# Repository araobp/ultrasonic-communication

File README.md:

**(Nov 2, 2018) I am going to rework on this project**

---
---
# Learning DSP with ultrasonic communications

## Background and motivation

STMicro gave me STM32L4(Arm Cortex-M4) evaluation board and a pair of MEMS microphones for free at [a trade show held in Makuhari city](https://www.st.com/content/st_com/en/about/events/events.html/techno-frontier-2018.html), Chiba, Japan. Thanks a lot to STMicro!

As an IoT hobyyist, I am becoming interested in DSP with MEMS mic.

Also thanks to this: https://github.com/y2kblog/NUCLEO-L476RG_DFSDM_PDM-Mic.

## Project goal

I am a DSP beginner, so I learn DSP by doing: realize "low-power narrow area networking" by cheap DSP and MEMS mic.

## My work so far

#### Project documentation

==> [Specification](https://docs.google.com/presentation/d/e/2PACX-1vSd3PQnKqmKbjcGNyNh_gygd175jgfzZYH5iwcEPqmmgiy7k3yYzqqHzfs7u-95jm_9hHgc0ugAvv2U/pub?start=false&loop=false&delayms=3000)

#### Platform: STM32L4 platform and FFT test code on MEMS mic

==> [Platform](./experiments/PLATFORM.md)

==> [Test code](./experiments/basic)

#### Mathematical formula expressing ultrasonic wave

I tested frequency-hopping to transmit data over ultra-sonic, resulting in very bad performance at low SNR in a noisy room. So I decided to employ chirp modulation in this project.

==> [Formula](./misc/Formula.ipynb)

#### Developing my original MEMS mic shield

I developed my original shield with Knowles MEMS mic:

- Knowles MEMS mic
- Character LCD
- LED (red)
- Tactile switche (reset)

#### Pinout of STM32L476RG

#### Working code

Code of the ultrasonic receiver running on STM32L476RG (Arm Cortex-M4L) and the original expansion board:

==> [Code](./receiver)

## Next challenge: I/Q modulation

I already made the code, but it did not fit into the RAM, so I will reduce the number of samples to 1024.

But the resolution of FFT w/ I/Q modulation will be still much better than the current implementation (FFT of 2048 samples w/o I/Q modulation).

## Experiments I made over the past month

I have made several experiments over the past month to study how data can be transmitted over ultra-sonic wave: FSK, hopping and chirp. The conclusion is to try Chirp modulation to fight with noise.

#### Ultrasonic communications experiment (FSK modulation)

==> [Experiment](./experiments/EXPERIMENT.md)

==> [Test code](./experiments/ultracom)

#### Ultrasonic communications experiment (Chirp modulation)

==> [Experiment2](./experiments/EXPERIMENT2.md)

==> [Test code](./experiments/chirp)

#### Ultrasonic communications experiment (Chirp modulation with compression)

==> [Experiment3](./experiments/EXPERIMENT3.md)

#### Ultrasonic communications experiment (time frame synchronization)

==> [Experiment4](./experiments/EXPERIMENT4.md)

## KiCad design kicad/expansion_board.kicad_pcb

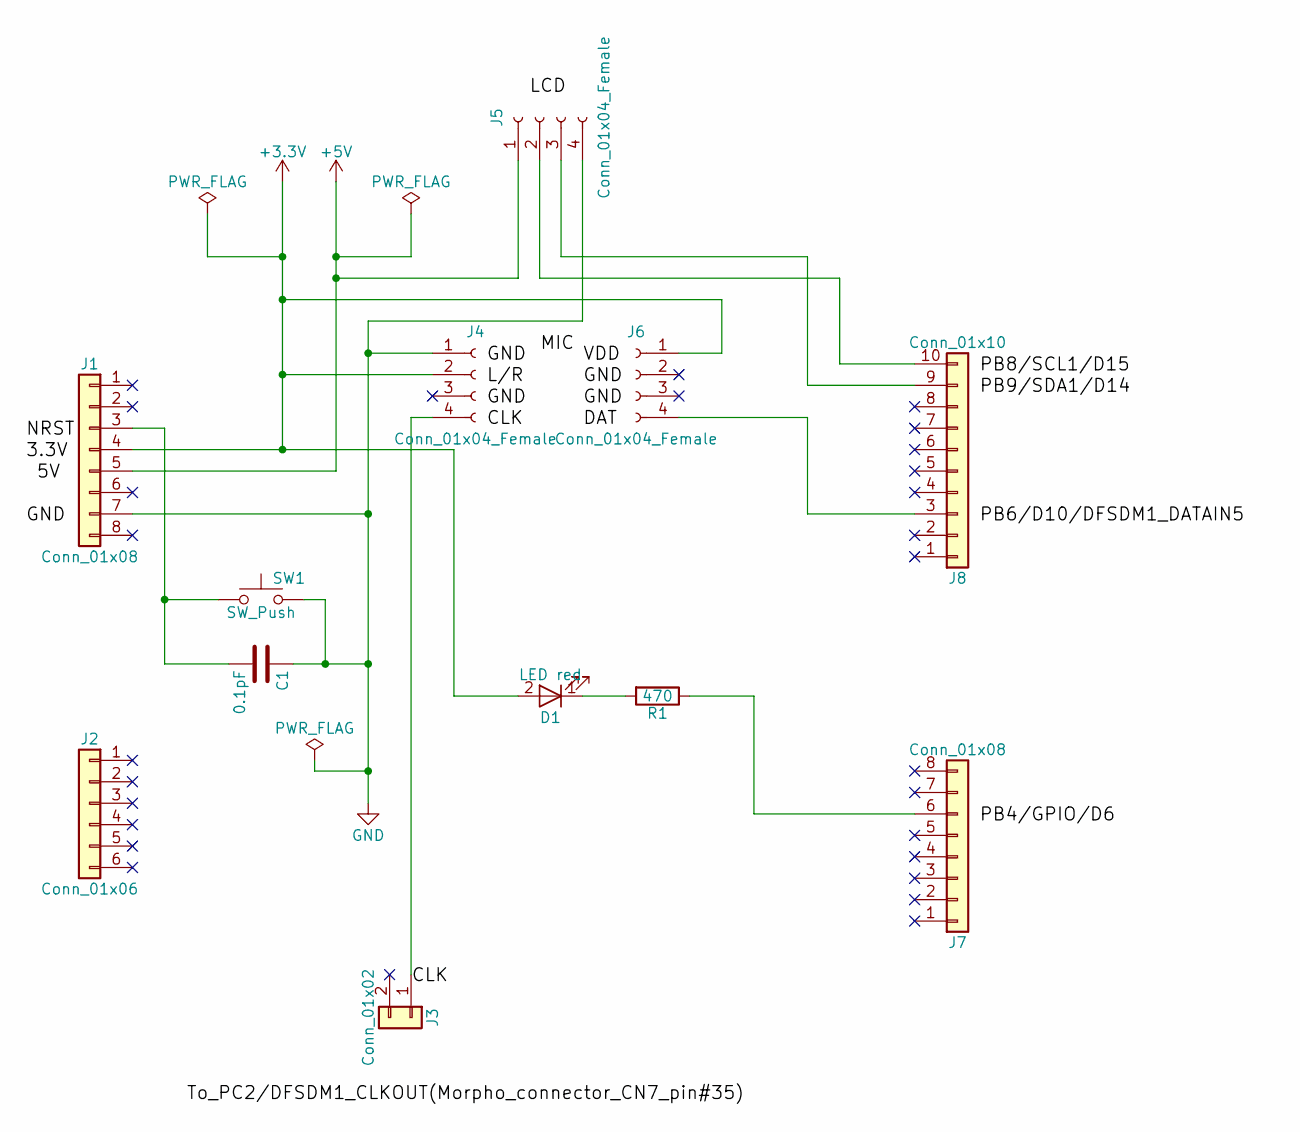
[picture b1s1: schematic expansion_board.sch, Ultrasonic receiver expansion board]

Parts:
C1: 0.1pF; Capacitor
D1: LED red; LED
J1, J7: Conn_01x08; Pin Header 8P
J2: Conn_01x06; Pin Header 6P
J3: Conn_01x02; Pin Header 2P
J4, J5, J6: Conn_01x04_Female; Pin Header 4P
J8: Conn_01x10; Pin Header 10P
R1: 470; Register
SW1: SW_Push; Tactile_switch_4P

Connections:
+3V3: D1.2 (A), J1.4, J4.2, J6.1
+5V: J1.5, J5.1
GND: C1.1, J1.7, J4.1, J5.4, SW1.2
unnamed: C1.2, J1.3, SW1.1
unnamed: D1.1 (K), R1.2
unnamed: J3.1, J4.4
unnamed: J5.2, J8.10
unnamed: J5.3, J8.9
unnamed: J6.4, J8.3
unnamed: J7.6, R1.1

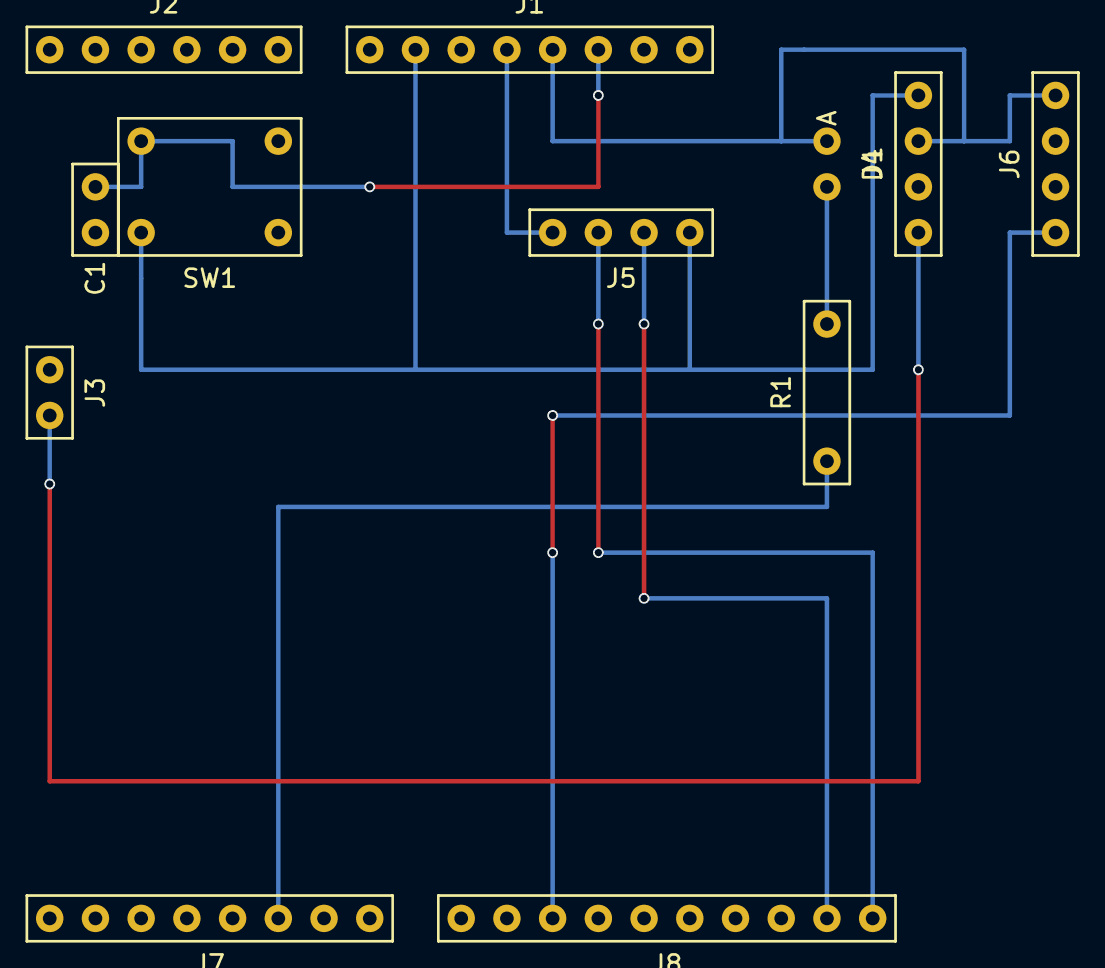
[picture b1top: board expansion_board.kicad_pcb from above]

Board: 2 copper layers, 12 parts (0 on the bottom side), 10 nets.

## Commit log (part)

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2018-05-22 Test 2
2018-05-22 README update
2018-05-26 Knowles MEMS mic
2018-05-26 S char
2018-05-26 HelloWorld spectrogram
2018-05-28 chirp experiment
2018-05-29 Chirp experiment with STM32L4
2018-05-30 speaker
2018-05-30 pic update
2018-06-10 First experiment of up chirp x down chirp
2018-06-10 Create EXPERIMENT2
2018-06-10 Rename EXPERIMENT2 to EXPERIMENT2.md
2018-06-13 frame sync test
2018-06-23 sync code
2018-06-23 bug fix
2018-06-24 magnitude history
2018-06-26 Bug fix
    Chirp calcuration was not correct.
2018-06-28 ChirpFrameGeneratorOnIQmodulation
2018-07-04 sync code tested
2018-07-07 Synchronous addition
    A combination of sinc5 and addition of two frames showed the best result.
2018-07-10 The first successful implementaion of receiver
2018-07-12 receiver src tree
2018-07-13 reciver
2018-07-13 Rename EXPERIMENTS4.md to EXPERIMENT4.md
